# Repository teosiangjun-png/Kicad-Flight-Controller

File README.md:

# Custom STM32F722 Flight Controller (Rev 1 Prototype)

A custom, bare-metal quadcopter flight controller engineered around the STMicroelectronics STM32F722 MCU running Betaflight.

This repository documents the KiCad schematics, PCB layout files, custom Betaflight target modifications, and a post-mortem technical analysis of bringing up a custom board through non-ideal hardware constraints and silicon-level clock workarounds.

---

## Technical Specifications

- **Microcontroller:** STM32F722RET6 / STM32F722 (ARM Cortex-M7 @ 216 MHz)
- **Target Firmware:** Betaflight (Custom fork derived from `BETAFPVF722`)
- **Physical Footprint:** 36 × 36 mm standard mounting pattern
- **Power Architecture:** Direct LiPo battery input with on-board buck/LDO stages for 5V and 3.3V rails
- **Peripheral Bus:** SPI for IMU communication, hardware UARTs for receiver and telemetry links

---

## Hardware Overview

### PCB Layout

### Schematic

---

## Repository Structure

```text
├── hardware/
│   ├── schematics/        # KiCad schematics (.kicad_sch)
│   ├── pcb/               # KiCad PCB layout and routing (.kicad_pcb)
│   └── gerbers/           # Fabrication and drill outputs
├── firmware/
│   ├── patches/           # Clock tree and pinout diffs against Betaflight master
│   └── target/            # Custom target configuration and pin mappings
└── docs/
    └── post-mortem.md     # Detailed engineering failure analysis and bring-up logs
```

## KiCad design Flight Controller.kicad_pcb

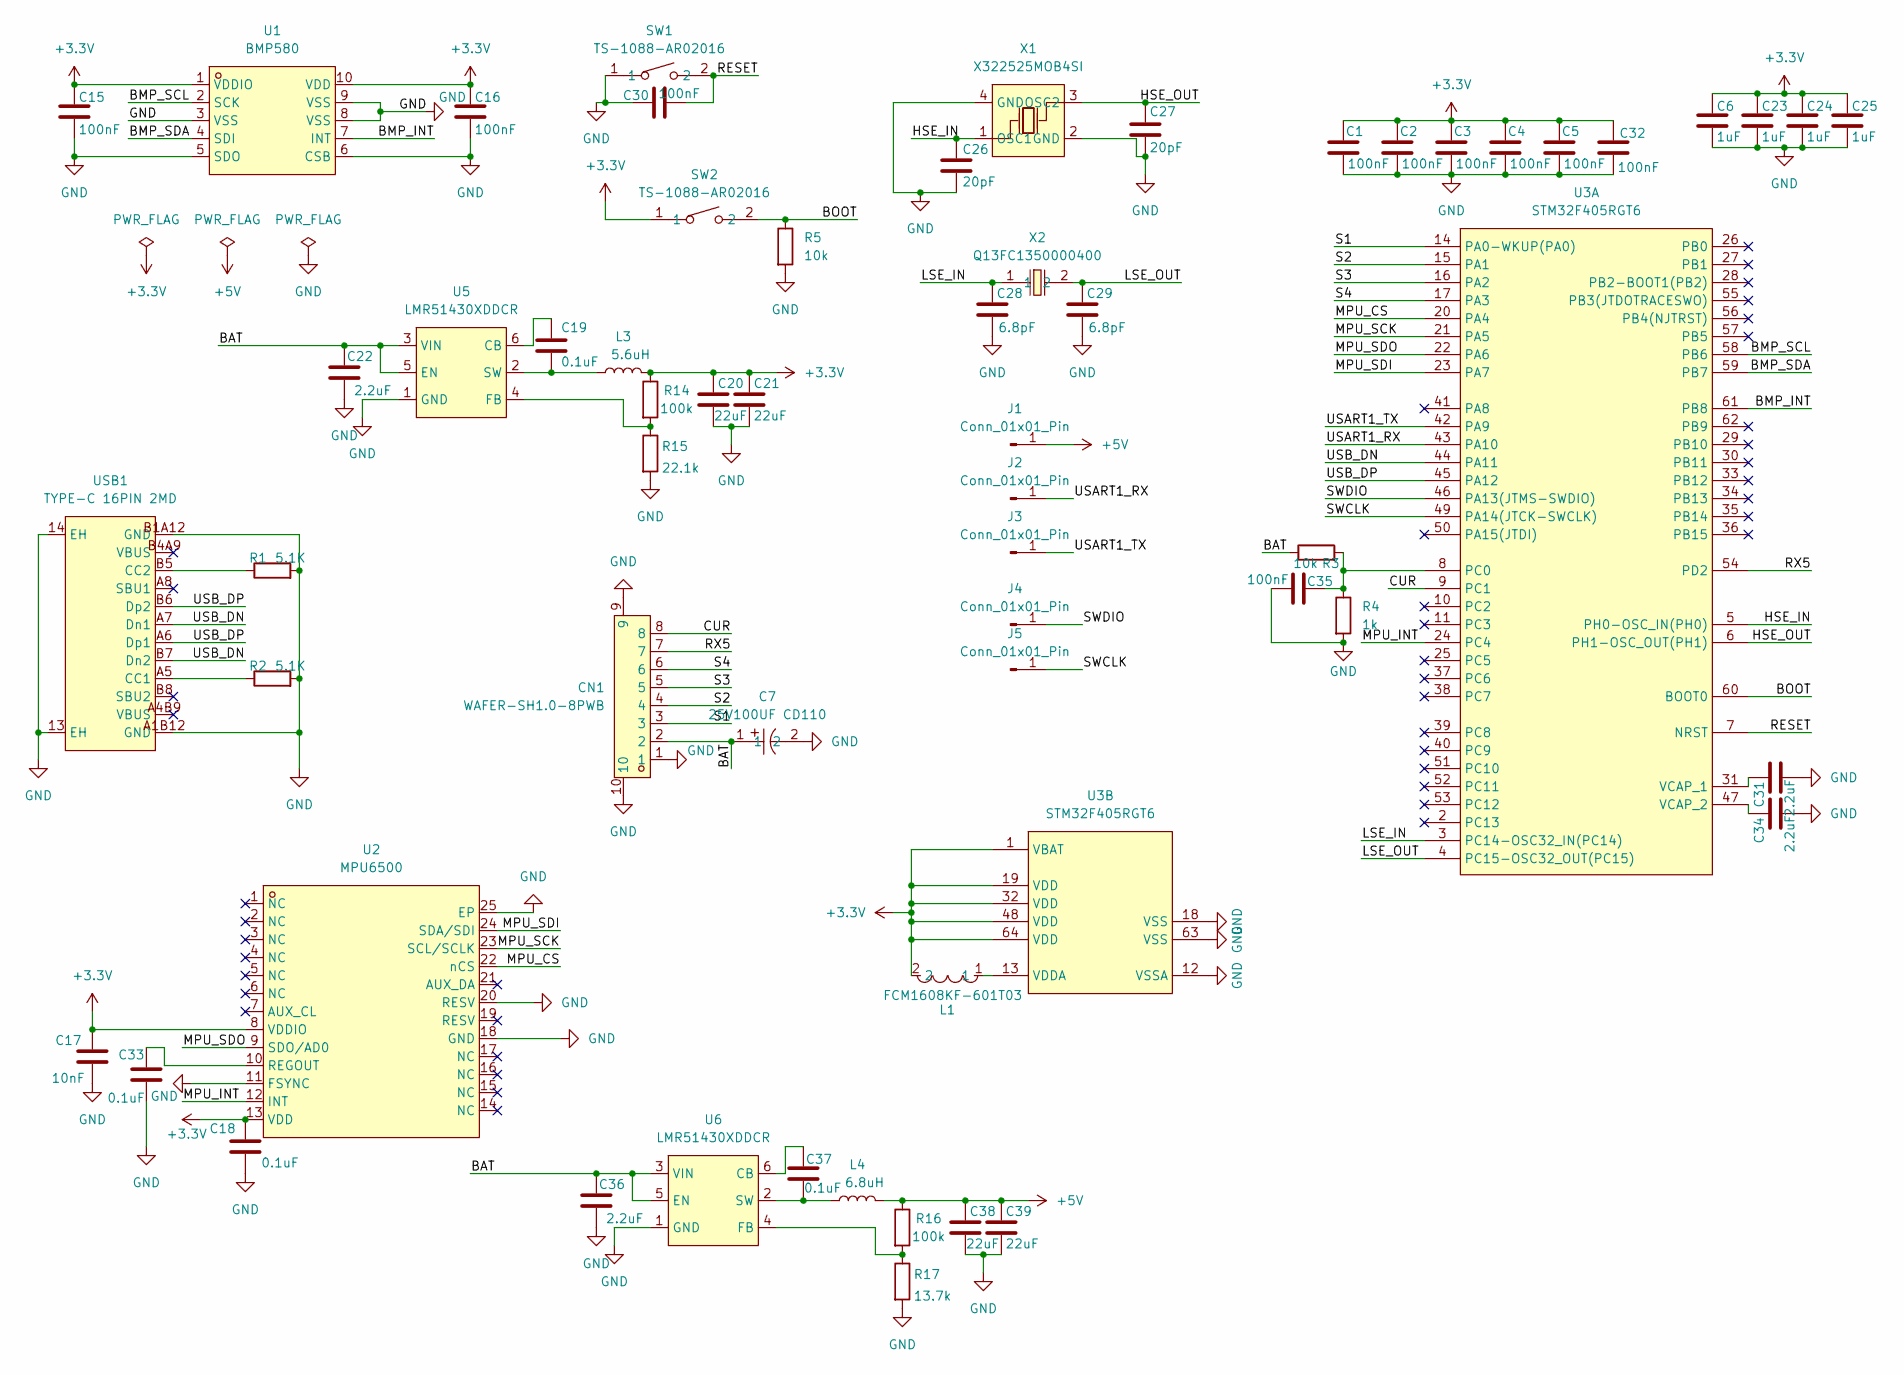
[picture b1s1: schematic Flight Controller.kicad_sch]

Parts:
C1, C2, C3, C4, C5, C15, C16, C30, C32, C35: 100nF; C_0402_1005Metric
C6, C23, C24, C25: 1uF; C_0402_1005Metric
C7: 25V100UF CD110; CAP-TH_BD6.3-P2.50-D0.5-FD; MPN 25V100uF CD110; LCSC Part C2960218
C17: 10nF; C_0402_1005Metric
C18, C19, C33, C37: 0.1uF; C_0402_1005Metric
C20, C21: 22uF; C_0805_2012Metric
C22, C36: 2.2uF; C_1206_3216Metric
C26, C27: 20pF; C_0402_1005Metric
C28, C29: 6.8pF; C_0402_1005Metric
C31, C34: 2.2uF; C_0603_1608Metric
C38, C39: 22uF; C_1206_3216Metric
CN1: WAFER-SH1.0-8PWB; CONN-SMD_8P-P1.00_XUNPU_WAFER-SH1.0-8PWB; MPN WAFER-SH1.0-8PWB; LCSC Part C3029347
J1, J2, J3, J4, J5: Conn_01x01_Pin; TestPoint_THTPad_2.0x2.0mm_Drill1.0mm
L1: FCM1608KF-601T03; L0603; MPN FCM1608KF-601T03; LCSC Part C141723
L3: 5.6uH; IND-SMD_L3.0-W3.0
L4: 6.8uH; IND-SMD_L3.0-W3.0
R1, R2: 5.1K; R_0402_1005Metric
R3, R5: 10k; R_0402_1005Metric
R4: 1k; R_0402_1005Metric
R14, R16: 100k; R_0402_1005Metric
R15: 22.1k; R_0402_1005Metric
R17: 13.7k; R_0402_1005Metric
SW1, SW2: TS-1088-AR02016; SW-SMD_L3.9-W3.0-P4.45; MPN TS-1088-AR02016; LCSC Part C720477
U1: BMP580; LGA-10_L2.0-W2.0-P0.50-TL_BMP580; MPN BMP580; LCSC Part C22391138
U2: MPU6500; QFN-24_L3.0-W3.0-P0.40-BL-EP; MPN MPU-6500; LCSC Part C50278
U3: STM32F405RGT6; LQFP-64_L10.0-W10.0-P0.50-LS12.0-BL; MPN STM32F405RGT6; LCSC Part C15742
U5, U6: LMR51430XDDCR; SOT-23-6_L2.9-W1.6-P0.95-LS2.8-BL; MPN LMR51430XDDCR; LCSC Part C5185863
USB1: TYPE-C 16PIN 2MD; USB-C-SMD_TYPE-C-16PIN-2MD-073; MPN TYPE-C 16PIN 2MD(073); LCSC Part C2765186
X1: X322525MOB4SI; CRYSTAL-SMD_4P-L3.2-W2.5-BL; MPN X322525MOB4SI; LCSC Part C9006
X2: Q13FC1350000400; FC-135R_L3.2-W1.5; MPN Q13FC13500004; LCSC Part C32346

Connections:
+3.3V: C1.1, C2.1, C3.1, C4.1, C5.1, C6.1, C15.1, C16.1, C17.1, C18.1, C20.1, C21.1, C23.1, C24.1, C25.1, C32.1, L1.2, L3.2, R14.1, SW2.1, U1.1 (VDDIO), U1.10 (VDD), U2.8 (VDDIO), U2.13 (VDD), U3.1 (VBAT), U3.19 (VDD), U3.32 (VDD), U3.48 (VDD), U3.64 (VDD)
+5V: C38.1, C39.1, J1.1 (Pin_1_1), L4.2, R16.1
/BAT: C7.1, C22.1, C36.1, CN1.2, R3.1, U5.3 (VIN), U5.5 (EN), U6.3 (VIN), U6.5 (EN)
/BMP_INT: U1.7 (INT), U3.61 (PB8)
/BMP_SCL: U1.2 (SCK), U3.58 (PB6)
/BMP_SDA: U1.4 (SDI), U3.59 (PB7)
/BOOT: R5.1, SW2.2, U3.60 (BOOT0)
/CUR: CN1.8, U3.9 (PC1)
/HSE_IN: C26.1, U3.5 (PH0-OSC_IN(PH0)), X1.1 (OSC1)
/HSE_OUT: C27.1, U3.6 (PH1-OSC_OUT(PH1)), X1.3 (OSC2)
/LSE_IN: C28.1, U3.3 (PC14-OSC32_IN(PC14)), X2.1
/LSE_OUT: C29.1, U3.4 (PC15-OSC32_OUT(PC15)), X2.2
/MPU_CS: U2.22 (nCS), U3.20 (PA4)
/MPU_INT: U2.12 (INT), U3.24 (PC4)
/MPU_SCK: U2.23 (SCL/SCLK), U3.21 (PA5)
/MPU_SDI: U2.24 (SDA/SDI), U3.23 (PA7)
/MPU_SDO: U2.9 (SDO/AD0), U3.22 (PA6)
/RESET: C30.2, SW1.2, U3.7 (NRST)
/RX5: CN1.7, U3.54 (PD2)
/S1: CN1.3, U3.14 (PA0-WKUP(PA0))
/S2: CN1.4, U3.15 (PA1)
/S3: CN1.5, U3.16 (PA2)
/S4: CN1.6, U3.17 (PA3)
/SWCLK: J5.1 (Pin_1_1), U3.49 (PA14(JTCK-SWCLK))
/SWDIO: J4.1 (Pin_1_1), U3.46 (PA13(JTMS-SWDIO))
/USART1_RX: J2.1 (Pin_1_1), U3.43 (PA10)
/USART1_TX: J3.1 (Pin_1_1), U3.42 (PA9)
/USB_DN: U3.44 (PA11), USB1.A7 (Dn1), USB1.B7 (Dn2)
/USB_DP: U3.45 (PA12), USB1.A6 (Dp1), USB1.B6 (Dp2)
GND: C1.2, C2.2, C3.2, C4.2, C5.2, C6.2, C7.2, C15.2, C16.2, C17.2, C18.2, C20.2, C21.2, C22.2, C23.2, C24.2, C25.2, C26.2, C27.2, C28.2, C29.2, C30.1, C31.2, C32.2, C33.2, C34.2, C35.1, C36.2, C38.2, C39.2, CN1.1, CN1.9, CN1.10, R1.2, R2.2, R4.2, R5.2, R15.2, R17.2, SW1.1, U1.3 (VSS), U1.5 (SDO), U1.6 (CSB), U1.8 (VSS), U1.9 (VSS), U2.11 (FSYNC), U2.18 (GND), U2.20 (RESV), U2.25 (EP), U3.12 (VSSA), U3.18 (VSS), U3.63 (VSS), U5.1 (GND), U6.1 (GND), USB1.13 (EH), USB1.14 (EH), USB1.A1B12 (GND), USB1.B1A12 (GND), X1.2 (GND), X1.4 (GND)
unnamed: C33.1, U2.10 (REGOUT)
unnamed: C35.2, R3.2, R4.1, U3.8 (PC0)
unnamed: C31.1, U3.31 (VCAP_1)
unnamed: C34.1, U3.47 (VCAP_2)
unnamed: L1.1, U3.13 (VDDA)
unnamed: C19.1, U5.6 (CB)
unnamed: R14.2, R15.1, U5.4 (FB)
unnamed: C19.2, L3.1, U5.2 (SW)
unnamed: C37.1, U6.6 (CB)
unnamed: R16.2, R17.1, U6.4 (FB)
unnamed: C37.2, L4.1, U6.2 (SW)
unnamed: R2.1, USB1.A5 (CC1)
unnamed: R1.1, USB1.B5 (CC2)

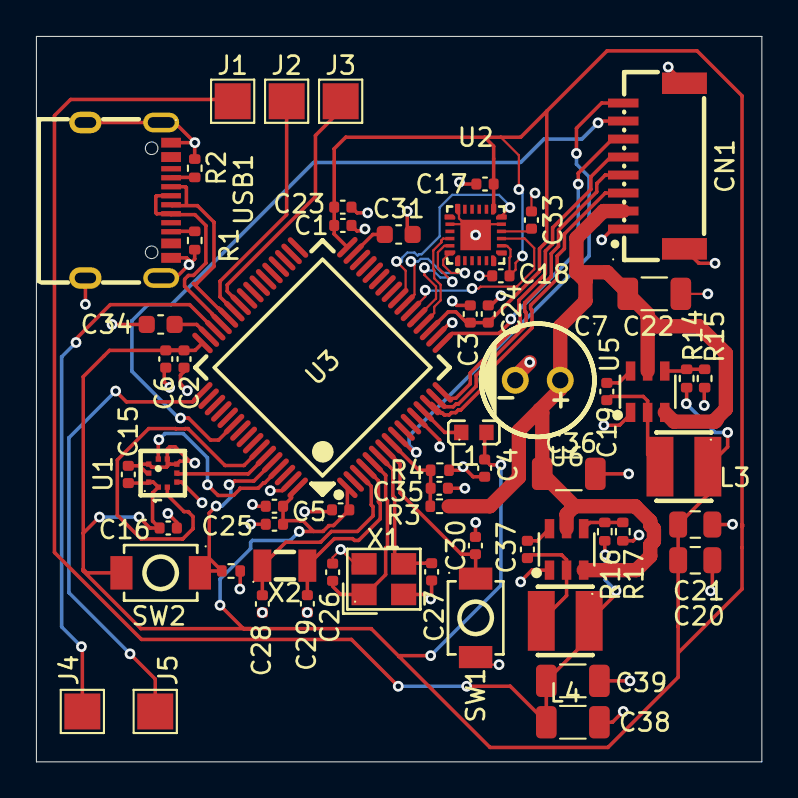
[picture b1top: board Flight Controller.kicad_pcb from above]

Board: 2 copper layers, 40.3 x 40.3 mm, 60 parts (0 on the bottom side), 43 nets.

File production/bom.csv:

Designator,Footprint,Quantity,Value,LCSC Part #
"C1, C15, C16, C2, C3, C30, C32, C35, C4, C5",0402,10,100nF,
C17,0402,1,10nF,
"C18, C19, C33, C37",0402,4,0.1uF,
"C20, C21",0805,2,22uF,
"C22, C36",1206,2,2.2uF,
"C23, C24, C25, C6",0402,4,1uF,
"C26, C27",0402,2,20pF,
"C28, C29",0402,2,6.8pF,
"C31, C34",0603,2,2.2uF,
"C38, C39",1206,2,22uF,
C7,CAP-TH_BD6.3-P2.50-D0.5-FD,1,25V100UF CD110,C2960218
CN1,CONN-SMD_8P-P1.00_XUNPU_WAFER-SH1.0-8PWB,1,WAFER-SH1.0-8PWB,C3029347
"J1, J2, J3, J4, J5",TestPoint_THTPad_2.0x2.0mm_Drill1.0mm,5,Conn_01x01_Pin,
L1,L0603,1,FCM1608KF-601T03,C141723
L3,IND-SMD_L3.0-W3.0,1,5.6uH,C18236327
L4,IND-SMD_L3.0-W3.0,1,6.8uH,C18236327
"R1, R2",0402,2,5.1K,
"R14, R16",0402,2,100k,
R15,0402,1,22.1k,
R17,0402,1,13.7k,
"R3, R5",0402,2,10k,
R4,0402,1,1k,
"SW1, SW2",SW-SMD_L3.9-W3.0-P4.45,2,TS-1088-AR02016,C720477
U1,LGA-10_L2.0-W2.0-P0.50-TL_BMP580,1,BMP580,C22391138
U2,QFN-24_L3.0-W3.0-P0.40-BL-EP,1,MPU6500,C50278
U3,LQFP-64_L10.0-W10.0-P0.50-LS12.0-BL,1,STM32F405RGT6,C118207
"U5, U6",SOT-23-6_L2.9-W1.6-P0.95-LS2.8-BL,2,LMR51430XDDCR,C5185863
USB1,USB-C-SMD_TYPE-C-16PIN-2MD-073,1,TYPE-C 16PIN 2MD,C2765186
X1,CRYSTAL-SMD_4P-L3.2-W2.5-BL,1,X322525MOB4SI,C9006
X2,FC-135R_L3.2-W1.5,1,Q13FC1350000400,C32346
